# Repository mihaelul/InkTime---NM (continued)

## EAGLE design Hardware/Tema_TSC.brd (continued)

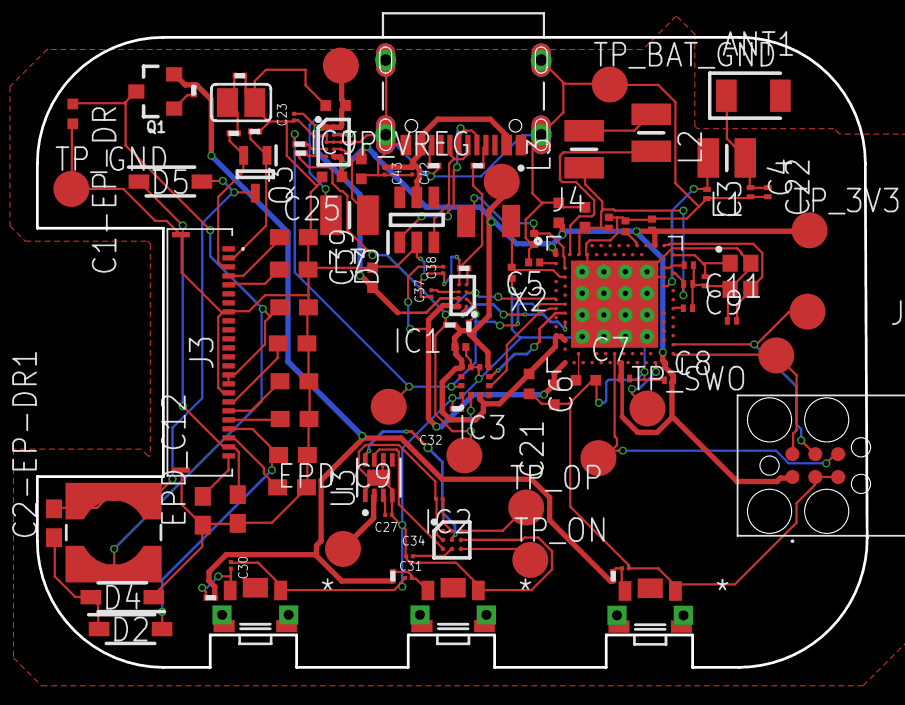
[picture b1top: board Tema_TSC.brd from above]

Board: 2 copper layers, 46.1 x 35.0 mm, 105 parts (0 on the bottom side), 67 nets.

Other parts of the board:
C2-EP-DR1: 4.7u/25V; NORDIC_NRF_3_RESC0603_N

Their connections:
unnamed 45: C2-EP-DR1.1; also elsewhere on the board
unnamed 46: C2-EP-DR1.2; also elsewhere on the board

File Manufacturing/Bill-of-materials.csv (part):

Qty,Value,Device,Package,Parts,Description,ARROW_PART_NUMBER,ARROW_PRICE-STOCK,AVAILABILITY,CHECK_PRICES,COPYRIGHT,DESCRIPTION,DIGI-KEY_PART_NUMBER_1,DIGI-KEY_PART_NUMBER_2,DIGI-KEY_PART_NUMBER_3,HEIGHT,JLCPCB,MANUFACTURER_NAME,MANUFACTURER_PART_NUMBER,MF,MFR_NAME,MOUSER_PART_NUMBER,MOUSER_PRICE-STOCK,MP,PACKAGE,POPULARITY,PRICE,PROD_ID,PURCHASE-URL,SNAPEDA_LINK,TP_SIGNAL_NAME,VALUE
1,,ESP32_C6_LIBRARY_7_JUMPER_SJ,ESP32_C6_LIBRARY_7_JUMPER_SJ,SJ1,"SMD solder JUMPER",,,,,,,,,,,,,,,,,,,,3,,,,,,
3,0,CPF0201D7K68C1_CPF0201D7K68C1,CPF0201D7K68C1_0201,"R2, R3, R4","7.68k 0201 Thin Film Surface Mount Fixed Resistor +/-0.5% 0.031W CPF0201D7K68C1",,,,,,,,,,,,,,,,,,,,,,,,,,
4,0.1uF,GRM011R60J152KE01L_2_GRM011R60J152KE01L,GRM011R60J152KE01L_2_CAPC0201X13N,"C23, C27, C34, C42","Check availability",,,"In Stock",https://www.snapeda.com/parts/GRM011R60J152KE01L/Murata/view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,,"                                                      SMD Capacitor X5R(EIA) with Capacitance: 1500pF Tol. 10%. Rated Voltage: 6.3Vdc                                              ",,,,,,,,Murata,,,,GRM011R60J152KE01L,"0201 Murata",,None,,,https://www.snapeda.com/parts/GRM011R60J152KE01L/Murata/view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,,
8,0.1uF/50V,NORDIC_NRF_3_CAPACITOR_0402_N,NORDIC_NRF_3_RESC0402_N,"EPD_C5, EPD_C6, EPD_C7, EPD_C8, EPD_C9, EPD_C10, EPD_C11, EPD_C12","Generic chip capacitor",,,,,,,,,,,,,,,,,,,,,,,,,,
1,0.47,CPF0201D7K68C1_CPF0201D7K68C1,CPF0201D7K68C1_0201,R1_EP_DR,"7.68k 0201 Thin Film Surface Mount Fixed Resistor +/-0.5% 0.031W CPF0201D7K68C1",,,,,,,,,,,,,,,,,,,,,,,,,,
1,1.0µF,NORDIC_NRF_3_CAPACITOR_0402_N,NORDIC_NRF_3_RESC0402_N,C15,"Generic chip capacitor",,,,,,,,,,,,,,,,,,,,,,,,,,
2,100nF,NORDIC_NRF_3_CAPACITOR_0201_L,NORDIC_NRF_3_RESC0201_L,"C7, C8","Generic chip capacitor",,,,,,,,,,,,,,,,,,,,,,,,,,
3,100nF,NORDIC_NRF_3_CAPACITOR_0201_N,NORDIC_NRF_3_RESC0201_N,"C5, C12, C19","Generic chip capacitor",,,,,,,,,,,,,,,,,,,,,,,,,,
1,100pF,NORDIC_NRF_3_CAPACITOR_0201_L,NORDIC_NRF_3_RESC0201_L,C11,"Generic chip capacitor",,,,,,,,,,,,,,,,,,,,,,,,,,
2,10K,CPF0201D7K68C1_CPF0201D7K68C1,CPF0201D7K68C1_0201,"R9, R_PWR_EPD","7.68k 0201 Thin Film Surface Mount Fixed Resistor +/-0.5% 0.031W CPF0201D7K68C1",,,,,,,,,,,,,,,,,,,,,,,,,,
4,10k,CPF0201D7K68C1_CPF0201D7K68C1,CPF0201D7K68C1_0201,"R2_EP_DR, R5, R7, R8","7.68k 0201 Thin Film Surface Mount Fixed Resistor +/-0.5% 0.031W CPF0201D7K68C1",,,,,,,,,,,,,,,,,,,,,,,,,,
3,10uF,NORDIC_NRF_3_CAPACITOR_0402_N,NORDIC_NRF_3_RESC0402_N,"C1-EP-DR, C24, C39","Generic chip capacitor",,,,,,,,,,,,,,,,,,,,,,,,,,
1,10µH,MLP2016SR47MT0S1_FTC252012SR47MBCA,MLP2016SR47MT0S1_INDC2016X100N,L2,"SMD / SMT Inductors (Coils), L=0.47?H, L x W x T :",,,,,,"SMD / SMT Inductors (Coils)"," L=0.47?H"," L x W x T :",,,,1mm,https://jlcpcb.com/partdetail/6763488-FTC252012SR47MBCA/C5832368,TDK,FTC252012SR47MBCA,,,,,,,,,,,
2,12pF,NORDIC_NRF_3_CAPACITOR_0201_L,NORDIC_NRF_3_RESC0201_L,"C1, C2","Generic chip capacitor",,,,,,,,,,,,,,,,,,,,,,,,,,
2,12pF,NORDIC_NRF_3_CAPACITOR_0201_N,NORDIC_NRF_3_RESC0201_N,"C17, C18","Generic chip capacitor",,,,,,,,,,,,,,,,,,,,,,,,,,
1,15nH,MLP2016SR47MT0S1_FTC252012SR47MBCA,MLP2016SR47MT0S1_INDC2016X100N,L3,"SMD / SMT Inductors (Coils), L=0.47?H, L x W x T :",,,,,,"SMD / SMT Inductors (Coils)"," L=0.47?H"," L x W x T :",,,,1mm,https://jlcpcb.com/partdetail/6763488-FTC252012SR47MBCA/C5832368,TDK,FTC252012SR47MBCA,,,,,,,,,,,
2,1pF,NORDIC_NRF_3_CAPACITOR_0201_L,NORDIC_NRF_3_RESC0201_L,"C3, C4","Generic chip capacitor",,,,,,,,,,,,,,,,,,,,,,,,,,
6,1uF,GRM011R60J152KE01L_2_GRM011R60J152KE01L,GRM011R60J152KE01L_2_CAPC0201X13N,"C29, C30, C31, C32, C37, C38","Check availability",,,"In Stock",https://www.snapeda.com/parts/GRM011R60J152KE01L/Murata/view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,,"                                                      SMD Capacitor X5R(EIA) with Capacitance: 1500pF Tol. 10%. Rated Voltage: 6.3Vdc                                              ",,,,,,,,Murata,,,,GRM011R60J152KE01L,"0201 Murata",,None,,,https://www.snapeda.com/parts/GRM011R60J152KE01L/Murata/view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,,
2,1uF/50V,NORDIC_NRF_3_CAPACITOR_0402_N,NORDIC_NRF_3_RESC0402_N,"EPD_C1, EPD_C2","Generic chip capacitor",,,,,,,,,,,,,,,,,,,,,,,,,,
1,2.2,CPF0201D7K68C1_CPF0201D7K68C1,CPF0201D7K68C1_0201,R_TYPE_SEL,"7.68k 0201 Thin Film Surface Mount Fixed Resistor +/-0.5% 0.031W CPF0201D7K68C1",,,,,,,,,,,,,,,,,,,,,,,,,,
3,2025-10-22_07-23-44_LIBRARY_EVP-AKE31ASW_EVP-AKE31A_PAN,2025-10-22_07-23-44_LIBRARY_EVP-AKE31ASW_EVP-AKE31A_PAN,2025-10-22_07-23-44_LIBRARY_SW_EVP-AKE31A_PAN,"SW_DN, SW_ENT, SW_UP",,,,,,"Copyright (C) 2025 Ultra Librarian. All rights reserved.",,P123437TR-ND,P123437CT-ND,P123437DKR-ND,,,Panasonic,EVP-AKE31A,,,,,,,,,,,,,
1,20V/4.2A/52mO/1.4W,ESP32_C6_LIBRARY_4_ESP32_WROVER_SPARKFUN-DISCRETESEMI_MOSFET_PCH-DMG2305UX-7,ESP32_C6_LIBRARY_4_ESP32_C6_LIBRARY_4_ESP32_C6_LIBRARY_4_ESP32_C6_LIBRARY_4_ESP32_WROVER_SPARKFUN-DISCRETESEMI_SOT23-3,Q1,"P-channel MOSFETs",,,,,,,,,,,,,,,,,,,,,,TRAN-14388,,,,20V/4.2A/52mO/1.4W
2,22uF,NORDIC_NRF_3_CAPACITOR_0402_N,NORDIC_NRF_3_RESC0402_N,"C25, C33","Generic chip capacitor",,,,,,,,,,,,,,,,,,,,,,,,,,
1,2450AT18B100E_2450AT18B100E,2450AT18B100E_2450AT18B100E,2450AT18B100E_ANTC3216X140N,ANT1,"Antennas 2.45GHz ANTENNA",2450AT18B100E,https://www.arrow.com/en/products/2450at18b100e/johanson-die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,,,,"Antennas 2.45GHz ANTENNA",,,,1.4mm,,"JOHANSON TECHNOLOGY",2450AT18B100E,,,609-2450AT18B100E,https://www.mouser.co.uk/ProductDetail/Johanson-Technology/2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,,,,,,,,,
1,3.9nH,MLP2016SR47MT0S1_FTC252012SR47MBCA,MLP2016SR47MT0S1_INDC2016X100N,L1,"SMD / SMT Inductors (Coils), L=0.47?H, L x W x T :",,,,,,"SMD / SMT Inductors (Coils)"," L=0.47?H"," L x W x T :",,,,1mm,https://jlcpcb.com/partdetail/6763488-FTC252012SR47MBCA/C5832368,TDK,FTC252012SR47MBCA,,,,,,,,,,,
1,32.768kHz,NORDIC_NRF_1_XTAL_32KHZ,NORDIC_NRF_1_XTAL_3215_N,X2,,,,,,,,,,,,,,,,,,,,,,,,,,,
1,32MHz,NORDIC_NRF_XTAL_32MHZ,NORDIC_NRF_BT-XTAL_2016_N,X1,,,,,,,,,,,,,,,,,,,,,,,,,,,
2,3K3,CPF0201D7K68C1_CPF0201D7K68C1,CPF0201D7K68C1_0201,"R17, R18","7.68k 0201 Thin Film Surface Mount Fixed Resistor +/-0.5% 0.031W CPF0201D7K68C1",,,,,,,,,,,,,,,,,,,,,,,,,,
1,4.7uF,GRM011R60J152KE01L_2_GRM011R60J152KE01L,GRM011R60J152KE01L_2_CAPC0201X13N,C43,"Check availability",,,"In Stock",https://www.snapeda.com/parts/GRM011R60J152KE01L/Murata/view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,,"                                                      SMD Capacitor X5R(EIA) with Capacitance: 1500pF Tol. 10%. Rated Voltage: 6.3Vdc                                              ",,,,,,,,Murata,,,,GRM011R60J152KE01L,"0201 Murata",,None,,,https://www.snapeda.com/parts/GRM011R60J152KE01L/Murata/view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,,
1,4.7uF/25V,NORDIC_NRF_3_CAPACITOR_0402_N,NORDIC_NRF_3_RESC0402_N,C2-EP-DR,"Generic chip capacitor",,,,,,,,,,,,,,,,,,,,,,,,,,
4,4.7µF,NORDIC_NRF_3_CAPACITOR_0402_N,NORDIC_NRF_3_RESC0402_N,"C6, C14, C20, C21","Generic chip capacitor",,,,,,,,,,,,,,,,,,,,,,,,,,
1,47nF,NORDIC_NRF_3_CAPACITOR_0201_N,NORDIC_NRF_3_RESC0201_N,C16,"Generic chip capacitor",,,,,,,,,,,,,,,,,,,,,,,,,,
1,503480-2400_503480-2400,503480-2400_503480-2400,503480-2400_5034802400,J3,"FFC & FPC Connectors 0.5mm FPC RA SMT Dual Contact 24Ckt",,,,,,"FFC & FPC Connectors 0.5mm FPC RA SMT Dual Contact 24Ckt",,,,1.87mm,,Molex,503480-2400,,,538-503480-2400,https://www.mouser.co.uk/ProductDetail/Molex/503480-2400?qs=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,,,,,,,,,
2,5k1,ERA-1AEB3401C_CPF0201D7K68C1,ERA-1AEB3401C_0201,"R1_USB, R2_USB","7.68k 0201 Thin Film Surface Mount Fixed Resistor +/-0.5% 0.031W CPF0201D7K68C1",,,,,,,,,,,,,,,,,,,,,,,,,,
1,68uH,ESP32_C6_LIBRARY_2_744043680IND_4828-WE-TPC_WRE,ESP32_C6_LIBRARY_2_IND_4828-WE-TPC_WRE,L5,,,,,,"Copyright (C) 2024 Ultra Librarian. All rights reserved.",,,,,,,,744043680,,"Wurth Electronics",,,,,,,,,,,
1,820pF,NORDIC_NRF_3_CAPACITOR_0201_L,NORDIC_NRF_3_RESC0201_L,C9,"Generic chip capacitor",,,,,,,,,,,,,,,,,,,,,,,,,,
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
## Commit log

2026-04-10 version 1
2026-04-10 version 1.1
2026-04-10 Add README
2026-04-16 pcb 2d updated
2026-04-16 add images
2026-04-21 final
2026-04-21 Add GNU General Public License v3
2026-04-21 Revise README with BOM and hardware specifications
